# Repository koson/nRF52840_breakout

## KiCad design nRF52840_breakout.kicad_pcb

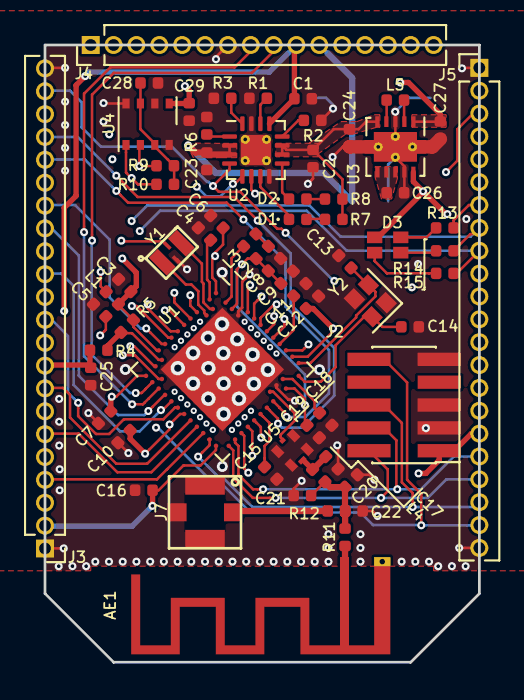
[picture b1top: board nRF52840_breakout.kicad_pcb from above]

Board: 4 copper layers, 24.1 x 34.3 mm, 66 parts (1 on the bottom side), 90 nets.

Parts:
AE1: Antenna_Shield; Texas_SWRA117D_2.4GHz_Right
C1, C2, C23, C24, C27: 10µF; C_0402_1005Metric
C3, C5, C7: 4.7µF; C_0402_1005Metric
C4, C10, C12, C16, C28, C29: 100nF; C_0402_1005Metric
C6, C8: 1µF; C_0402_1005Metric
C9: 47nF; C_0402_1005Metric
C11, C19, C21: N.C.; C_0402_1005Metric
C13, C14: 6pF; C_0402_1005Metric
C15: 820pF; C_0402_1005Metric
C17, C20: 1pF; C_0402_1005Metric
C18: 100pF; C_0402_1005Metric
C22: 1.2pF; C_0402_1005Metric
C25: NC; C_0402_1005Metric
C26: 0.1µF; C_0402_1005Metric
D1: GRN; LED_0402_1005Metric
D2: RED; LED_0402_1005Metric
D3: LTST-C19HE1WT
J2: Conn_ARM_JTAG_SWD_10; PinHeader_2x05_P1.27mm_Vertical_SMD
J3, J5: Conn_01x22; PinHeader_1x22_P1.27mm_Vertical
J4: Conn_01x16; PinHeader_1x16_P1.27mm_Vertical
J6: S2B-PH-SM4-TB(LF)(SN); JST_PH_S2B-PH-SM4-TB_LF__SN_
J7: Conn_Coaxial; CON_AMP_A-1JB
L1: NC; L_0402_1005Metric
L2: 15nH; L_0402_1005Metric
L3: 10µH; L_0402_1005Metric
L4: 3.9nH; L_0402_1005Metric
L5: 1.5µH; L_0402_1005Metric
R1: 46.4k; R_0402_1005Metric
R2: 1.18k; R_0402_1005Metric
R3: 1.13k; R_0402_1005Metric
R4: NC; R_0402_1005Metric
R5, R11, R12: 0R; R_0402_1005Metric
R6: 10k; R_0402_1005Metric
R7, R8, R13, R14, R15: 1.5k; R_0402_1005Metric
R9, R10: 4.7k; R_0402_1005Metric
U1: nRF52840; Nordic_AQFN-73-1EP_7x7mm_P0.5mm
U2: BQ24072; VQFN-16-1EP_3x3mm_P0.5mm_EP1.68x1.68mm_ThermalVias
U3: TPS63031; Texas_DRC0010J_ThermalVias
U4: BME680; Bosch_LGA-8_3x3mm_P0.8mm_ClockwisePinNumbering
U5: MM8130-2600RA2; MM8930_2620
Y1: SiT1533; Crystal_SMD_2012-4Pin_2.2mmx1.4mm
Y2: 32MHz-XRCGB32M000F1H00R0; Crystal_SMD_2016-4Pin_2.0x1.6mm

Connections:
D+: J4.8, U1.AD6
D-: J4.9, U1.AD4
GND: AE1.2, C1.2, C2.2, C3.2, C4.2, C5.2, C6.2, C7.2, C8.2, C9.2, C10.2, C11.2, C12.2, C13.1, C14.1, C15.2, C16.2, C17.1, C18.2, C19.2, C20.1, C21.1, C22.2, C23.2, C24.2, C25.2, C26.2, C27.2, C28.1, C29.1, J2.3, J2.5, J2.9, J3.1, J3.22, J4.7, J5.1, J5.22, J6.2, J6.S1, J7.2, R1.2, R2.2, R3.2, R6.1, U1.B7, U1.EP, U1.F23, U2.8, U2.15, U2.17, U3.3, U3.9, U3.11, U4.1, U4.5, U4.7, U5.3, Y1.2, Y2.1, Y2.3
unnamed: AE1.1, R11.1
unnamed: C4.1, U1.C1
unnamed: C5.1, U1.AC5
unnamed: C11.1, U1.A18
unnamed: C13.2, U1.A23, Y2.2
unnamed: C14.2, U1.B24, Y2.4
unnamed: C15.1, U1.N24
unnamed: C17.2, L4.2, U5.2
unnamed: C18.1, U1.D23
unnamed: C8.1, C9.1, C19.1, L2.1, U1.B5, U1.E24
unnamed: C20.2, C21.2, C22.1, L4.1, R11.2, R12.2
unnamed: C26.1, U3.6, U3.7, U3.8
unnamed: D1.1, U2.7
unnamed: D1.2, R7.1
unnamed: D2.1, U2.9
unnamed: D2.2, R8.1
unnamed: D3.1, R13.1
unnamed: D3.2, R14.1
unnamed: D3.3, R15.1
unnamed: J7.1, R12.1
unnamed: L1.2, U1.AB2
unnamed: L2.2, L3.1
unnamed: L3.2, U1.B3
unnamed: L5.1, U3.4
unnamed: L5.2, U3.2
unnamed: R1.1, U2.14
unnamed: R2.1, U2.12
unnamed: R3.1, U2.16
unnamed: R4.1, R5.1, U1.Y2
unnamed: R6.2, U2.1
unnamed: U1.D2, Y1.3
unnamed: U1.F2, Y1.1
unnamed: U1.H23, U5.1
P0.02_AIN0: J4.16, U1.A12
P0.03_AIN1: J3.21, U1.B13, U2.4
P0.04_AIN2: J4.4, U1.J1
P0.05_AIN3: J4.3, U1.K2
P0.06: J4.2, U1.L1
P0.07: J4.1, U1.M2
P0.08: J3.20, U1.N1
P0.09_NFC1: J3.19, U1.L24
P0.10_NFC2: J3.18, U1.J24
P0.11: J3.17, U1.T2
P0.12: J3.16, U1.U1
P0.13: J3.15, U1.AD8
P0.14: J3.14, U1.AC9
P0.15: J3.13, U1.AD10
P0.16: J3.12, U1.AC11
P0.17: J3.11, U1.AD12
P0.19: J3.10, U1.AC15
P0.20: J3.8, U1.AD16
P0.21: J3.7, U1.AC17
P0.22: J3.6, U1.AD18
P0.23: J3.5, U1.AC19
P0.24: J3.4, U1.AD20
P0.25: J3.3, U1.AC21
P0.26: J4.6, U1.G1, U2.6
P0.27: J4.5, U1.H2, U2.5
P0.28_AIN4: J4.15, U1.B11
P0.29_AIN5: J4.14, U1.A10
P0.30_AIN6: J4.13, U1.B9
P0.31_AIN7: J4.12, U1.A8
P1.00_SWO: J2.6, J5.20, U1.AD22
P1.01: J5.16, U1.Y23
P1.02: J5.15, U1.W24
P1.03: J5.14, U1.V23
P1.04: J5.13, U1.U24
P1.05: J5.12, U1.T23
P1.06: J5.11, U1.R24
P1.07: J5.10, U1.P23
P1.08: J5.9, R9.1, R15.2, U1.P2, U4.3
P1.09: J5.8, R10.1, R14.2, U1.R1, U4.4
P1.10: J5.7, R13.2, U1.A20
P1.11: J5.6, U1.B19
P1.12: J5.5, U1.B17
P1.13: J5.4, U1.A16
P1.14: J5.3, U1.B15
P1.15: J5.2, U1.A14
P1.18_RESET: J2.10, J5.21, U1.AC13
SWDCLK: J2.4, J5.18, U1.AA24
SWDIO: J2.2, J5.19, U1.AC24
VBUS_nRF: C1.1, C7.1, J4.10, U1.AD2, U2.13
VDDH: C25.1, J3.9, R4.2
VDDIO: C28.2, R9.2, R10.2, U4.2, U4.6
VDD_BAT: C23.1, J4.11, J6.1, U2.2, U2.3
VDD_nRF: C3.1, C6.1, C10.1, C12.1, C16.1, C27.1, C29.2, D3.4, J2.1, J3.2, J5.17, L1.1, R5.2, U1.A22, U1.AD14, U1.AD23, U1.B1, U1.W1, U3.1, U3.10, U4.8, Y1.4
V_SYS: C2.1, C24.1, R7.2, R8.2, U2.10, U2.11, U3.5

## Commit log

2024-04-09 kicad
